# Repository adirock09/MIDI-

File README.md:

# MIRA-Custom-MIDI-
<br>

<br>
I started with layout It has 40 Keys in 10 x 4 Layout.Top two layers are for High octave and bottom two for Low octave the three sliders are for Filter,Reverb,Modulation and three encoders are for Volume, Tempo, Track control.I used Matrix so it uses less Gpios, It is based on Raspberry Pico.
PCB made in Kicad and modeling done in Fusion 360. Firmware is written in circuit python and uses Adafruit MIDI Library.

## Bill of Materials (BOM)

| Index | Component | Part Number | Source | Quantity | Unit Price (USD) | Total Price (USD) | Notes |
|------|-----------|-------------|--------|----------|------------------|------------------|------|
| 1 | Bittersweet Switch | MX2A-HC1B | stackskb.com | (Pack of 45)  × 1 | 17 | 17 | |
| 2 | Keycaps Set | MX Compatible Keycaps | meckeys.com | 8(pack of 5) | 1.1 | 8.8 | For 40 keys |
| 3 | Signal Diode | 1N4148TR | makerbazar.in | 4(pack of 10) | 0.15 | 0.6 | |
| 4 | Raspberry Pi Pico | SC0917 | makerbazar.in | 1 | 6.12 | 6.12 | |
| 5 | Slide Potentiometer 10K | PTL60-15R0-103B2 | Existing | 3 | 0 | Already have | |
| 6 | PCB Fabrication | SeedStudio PCB | seeedstudio.com | 1 | 51.11 |51.11 | |
| 7 | PCB Shipping | seedstudio Shipping | seeedstudio.com | 27.37 |  | 27.37 | |
| 8 | Rotary Encoder | EC11 | Existing | 3 | 0 | 0 | Already have |
| 9 | M3 Screws | M3x16mm | Existing | 4 | 0 | 0 | Already have |
| 10 | M3 Heat-set Inserts | M3 Heatset | Existing | 4 | 0 | 0 | Already have |

### Total Project Cost
**$111**

## Schematic & PCB
<br>
<br>

<br>

## 3d Render
<br>

<br>

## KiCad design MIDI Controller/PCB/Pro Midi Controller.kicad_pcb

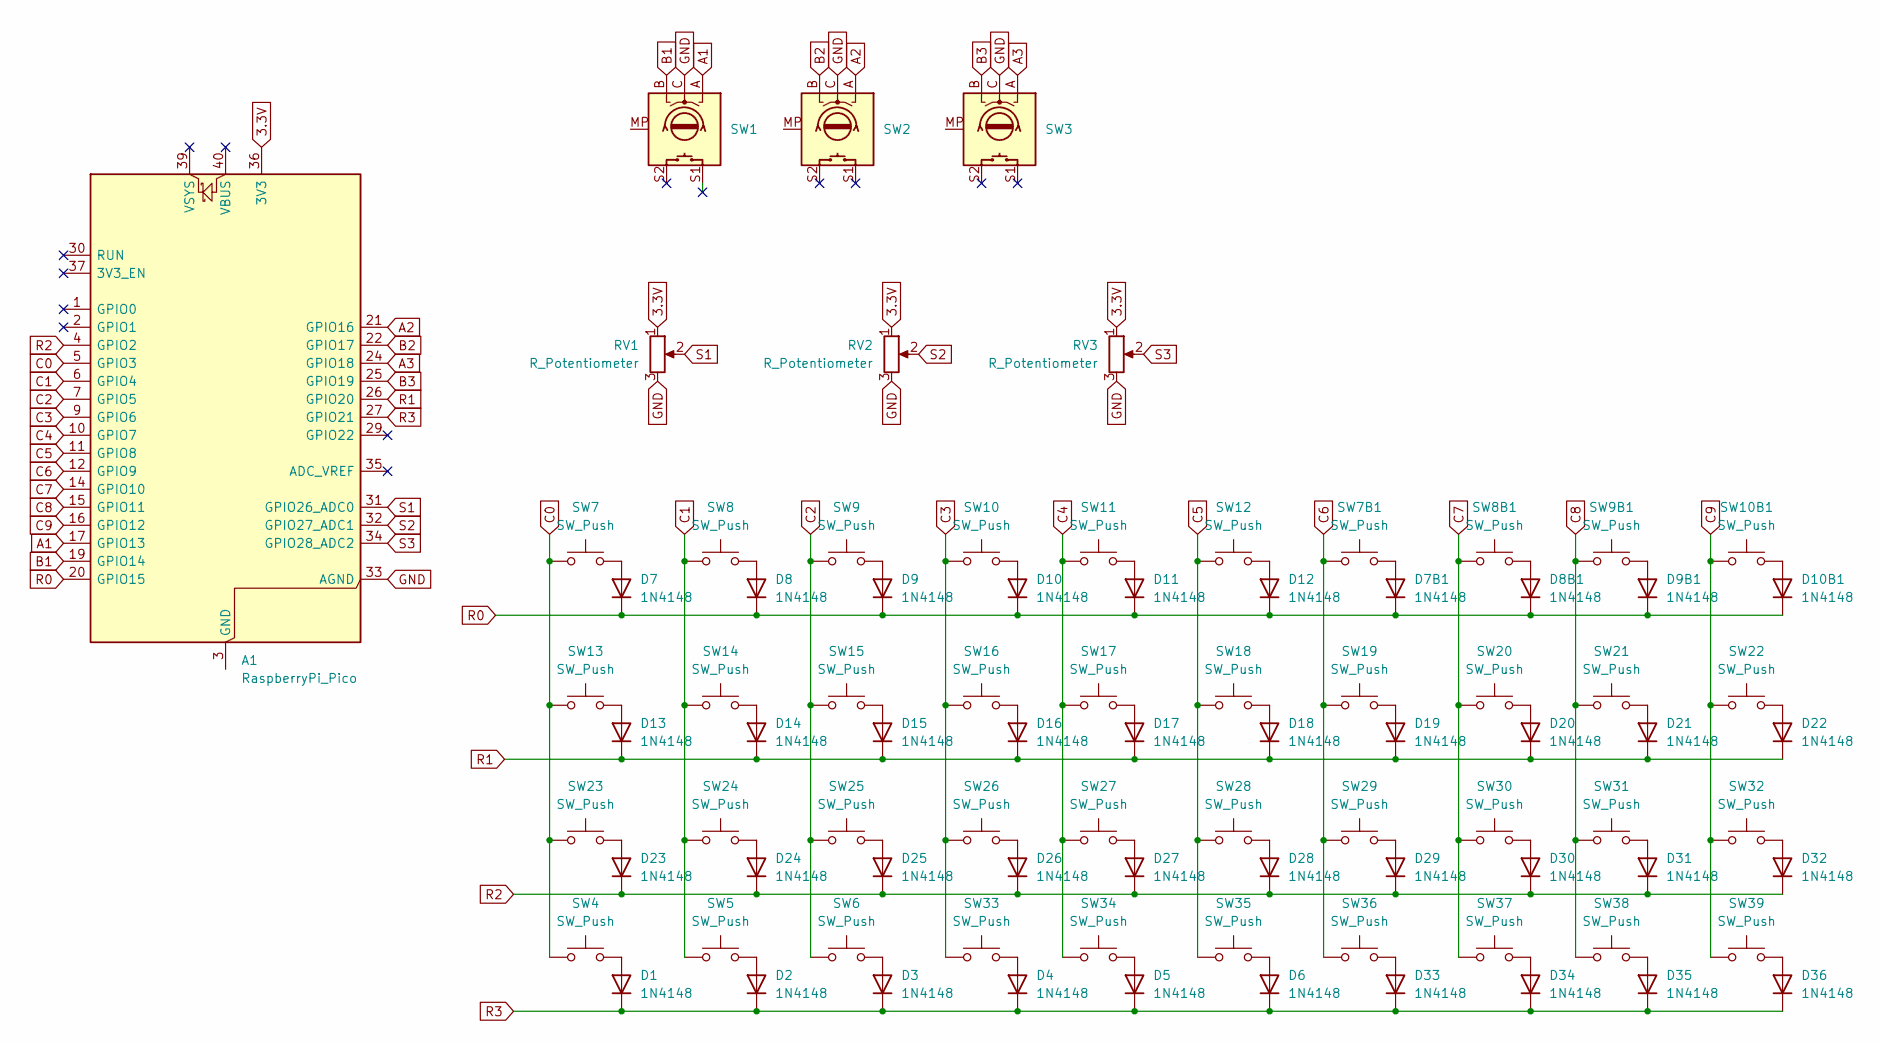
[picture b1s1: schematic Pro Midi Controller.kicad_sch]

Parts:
A1: RaspberryPi_Pico; RaspberryPi_Pico_Common_Unspecified
D1, D2, D3, D4, D5, D6, D7, D7B1, D8, D8B1, D9, D9B1, D10, D10B1, D11, D12, D13, D14, D15, D16, D17, D18, D19, D20, D21, D22, D23, D24, D25, D26, D27, D28, D29, D30, D31, D32, D33, D34, D35, D36: 1N4148; D_DO-35_SOD27_P7.62mm_Horizontal
RV1, RV2, RV3: R_Potentiometer; Potentiometer_Bourns_PTA6043_Single_Slide
SW1, SW2, SW3: RotaryEncoder_Switch_MP; RotaryEncoder_Alps_EC11E-Switch_Vertical_H20mm
SW4, SW5, SW6, SW7, SW7B1, SW8, SW8B1, SW9, SW9B1, SW10, SW10B1, SW11, SW12, SW13, SW14, SW15, SW16, SW17, SW18, SW19, SW20, SW21, SW22, SW23, SW24, SW25, SW26, SW27, SW28, SW29, SW30, SW31, SW32, SW33, SW34, SW35, SW36, SW37, SW38, SW39: SW_Push; SW_Cherry_MX_1.00u_PCB

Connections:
3.3V: A1.36 (3V3), RV1.1, RV2.1, RV3.1
A1: A1.17 (GPIO13), SW1.A
A2: A1.21 (GPIO16), SW2.A
A3: A1.24 (GPIO18), SW3.A
B1: A1.19 (GPIO14), SW1.B
B2: A1.22 (GPIO17), SW2.B
B3: A1.25 (GPIO19), SW3.B
C0: A1.5 (GPIO3), SW4.1, SW7.1, SW13.1, SW23.1
C1: A1.6 (GPIO4), SW5.1, SW8.1, SW14.1, SW24.1
C2: A1.7 (GPIO5), SW6.1, SW9.1, SW15.1, SW25.1
C3: A1.9 (GPIO6), SW10.1, SW16.1, SW26.1, SW33.1
C4: A1.10 (GPIO7), SW11.1, SW17.1, SW27.1, SW34.1
C5: A1.11 (GPIO8), SW12.1, SW18.1, SW28.1, SW35.1
C6: A1.12 (GPIO9), SW7B1.1, SW19.1, SW29.1, SW36.1
C7: A1.14 (GPIO10), SW8B1.1, SW20.1, SW30.1, SW37.1
C8: A1.15 (GPIO11), SW9B1.1, SW21.1, SW31.1, SW38.1
C9: A1.16 (GPIO12), SW10B1.1, SW22.1, SW32.1, SW39.1
GND: A1.33 (AGND), RV1.3, RV2.3, RV3.3, SW1.C, SW2.C, SW3.C
unnamed: A1.3 (GND), A1.8 (GND), A1.13 (GND), A1.18 (GND), A1.23 (GND), A1.28 (GND), A1.38 (GND)
unnamed: D1.2 (A), SW4.2
unnamed: D2.2 (A), SW5.2
unnamed: D3.2 (A), SW6.2
unnamed: D4.2 (A), SW33.2
unnamed: D5.2 (A), SW34.2
unnamed: D6.2 (A), SW35.2
unnamed: D7.2 (A), SW7.2
unnamed: D7B1.2 (A), SW7B1.2
unnamed: D8.2 (A), SW8.2
unnamed: D8B1.2 (A), SW8B1.2
unnamed: D9.2 (A), SW9.2
unnamed: D9B1.2 (A), SW9B1.2
unnamed: D10.2 (A), SW10.2
unnamed: D10B1.2 (A), SW10B1.2
unnamed: D11.2 (A), SW11.2
unnamed: D12.2 (A), SW12.2
unnamed: D13.2 (A), SW13.2
unnamed: D14.2 (A), SW14.2
unnamed: D15.2 (A), SW15.2
unnamed: D16.2 (A), SW16.2
unnamed: D17.2 (A), SW17.2
unnamed: D18.2 (A), SW18.2
unnamed: D19.2 (A), SW19.2
unnamed: D20.2 (A), SW20.2
unnamed: D21.2 (A), SW21.2
unnamed: D22.2 (A), SW22.2
unnamed: D23.2 (A), SW23.2
unnamed: D24.2 (A), SW24.2
unnamed: D25.2 (A), SW25.2
unnamed: D26.2 (A), SW26.2
unnamed: D27.2 (A), SW27.2
unnamed: D28.2 (A), SW28.2
unnamed: D29.2 (A), SW29.2
unnamed: D30.2 (A), SW30.2
unnamed: D31.2 (A), SW31.2
unnamed: D32.2 (A), SW32.2
unnamed: D33.2 (A), SW36.2
unnamed: D34.2 (A), SW37.2
unnamed: D35.2 (A), SW38.2
unnamed: D36.2 (A), SW39.2
R0: A1.20 (GPIO15), D7.1 (K), D7B1.1 (K), D8.1 (K), D8B1.1 (K), D9.1 (K), D9B1.1 (K), D10.1 (K), D10B1.1 (K), D11.1 (K), D12.1 (K)
R1: A1.26 (GPIO20), D13.1 (K), D14.1 (K), D15.1 (K), D16.1 (K), D17.1 (K), D18.1 (K), D19.1 (K), D20.1 (K), D21.1 (K), D22.1 (K)
R2: A1.4 (GPIO2), D23.1 (K), D24.1 (K), D25.1 (K), D26.1 (K), D27.1 (K), D28.1 (K), D29.1 (K), D30.1 (K), D31.1 (K), D32.1 (K)
R3: A1.27 (GPIO21), D1.1 (K), D2.1 (K), D3.1 (K), D4.1 (K), D5.1 (K), D6.1 (K), D33.1 (K), D34.1 (K), D35.1 (K), D36.1 (K)
S1: A1.31 (GPIO26_ADC0), RV1.2
S2: A1.32 (GPIO27_ADC1), RV2.2
S3: A1.34 (GPIO28_ADC2), RV3.2

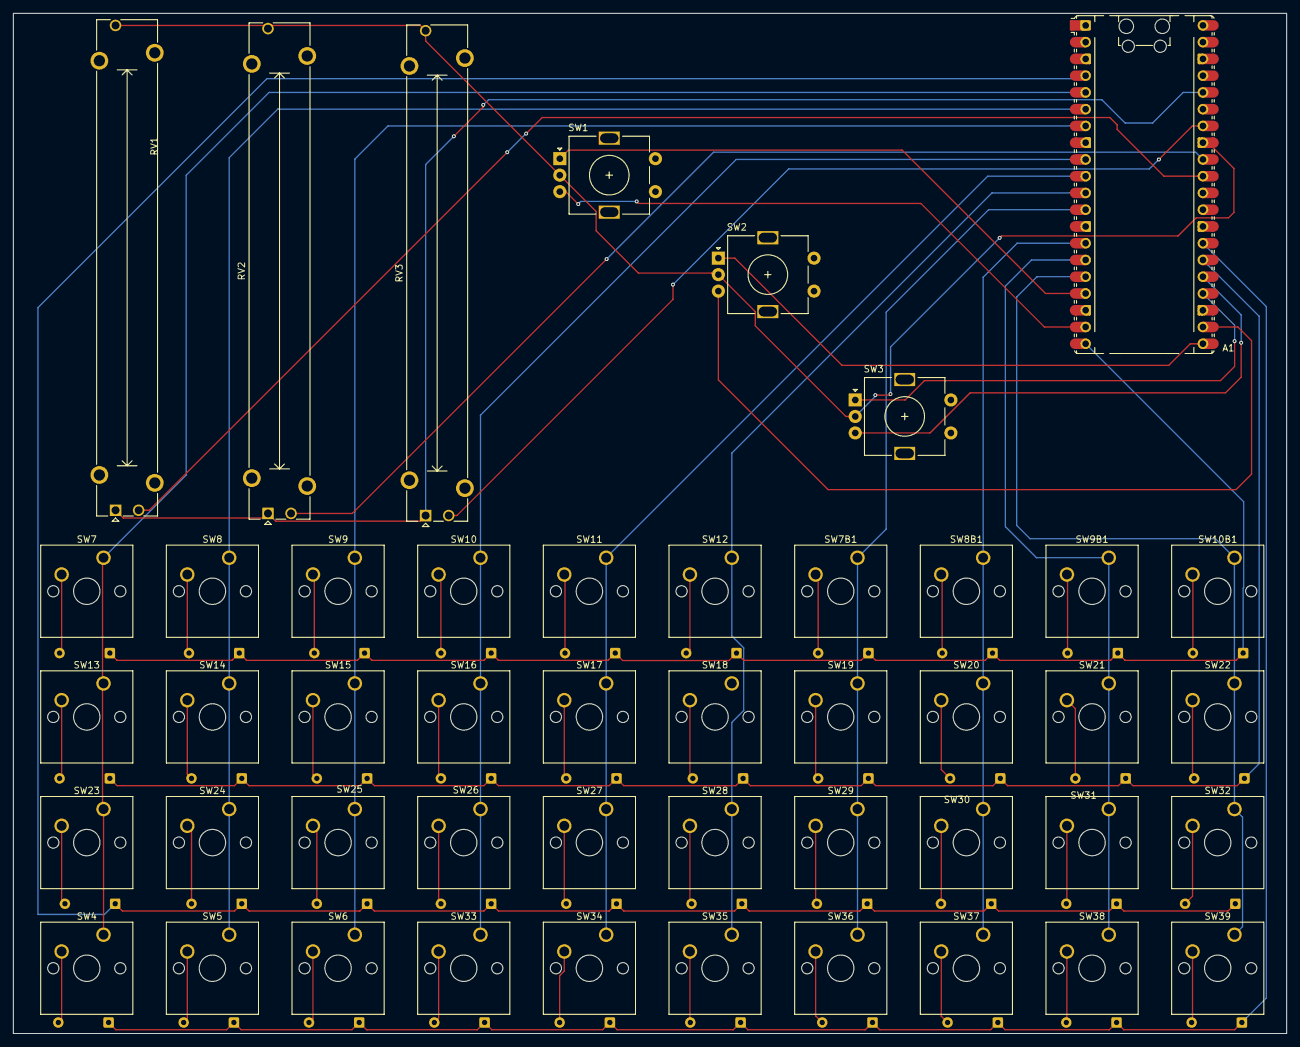
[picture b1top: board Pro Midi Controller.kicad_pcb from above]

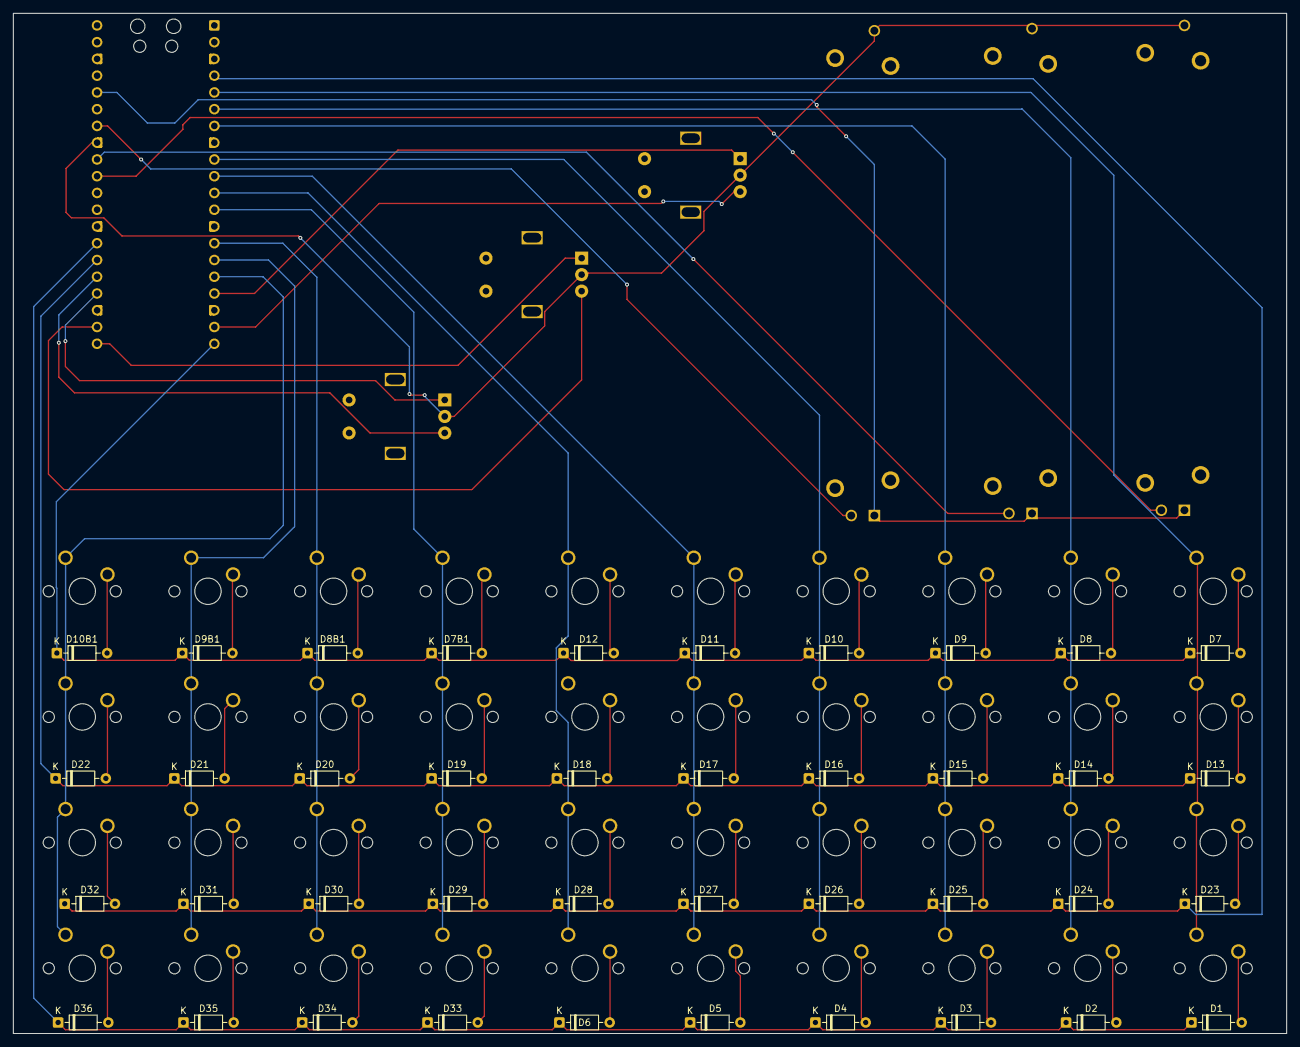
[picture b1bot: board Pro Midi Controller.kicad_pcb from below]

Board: 2 copper layers, 193.0 x 154.7 mm, 87 parts (40 on the bottom side), 66 nets.
